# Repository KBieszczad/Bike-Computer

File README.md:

# Custom IoT Bike Computer

A low-power custom bicycle computer featuring speed measurement, GPS tracking, environmental sensing, and an OLED display. The hardware is designed from scratch with a custom PCB created in KiCad.

## Description

This project aims to build a standalone, power-efficient bike computer. At its core is the Seeed Studio **XIAO nRF52840**, a very energy efficient microcontroller with native Bluetooth Low Energy support.

The device combines data from a classic magnetic reed switch (for precise speed and distance tracking) with an external GPS module for recording traces. Additionally, it integrates a BME280 sensor to monitor environmental conditions (temperature, humidity, and barometric pressure).

### Technical Features
* **Super-Loop Architecture:** Runs on a non-blocking state machine utilizing hardware interrupts (ISR) and atomics for exact speed calculation and UI rendering, completely avoiding `delay()` functions.
* **Persistent Storage (LittleFS):** Automatically saves user settings, wheel circumference, and route history to the internal non-volatile flash memory.
* **GPS Trace Recording:** Caches GPS coordinates in the background while moving and writes directly to flash. Traces can be directly exported over USB Serial to a raw `.gpx` file compatible with for example Strava.
* **Dynamic Power Management:** Implements multiple power modes (Normal, Eco, Ultra Eco). The device sends standard CASIC protocol sleep commands to the GPS module and hardware sleep flags to the BME280 sensor to drastically cut power consumption when full tracking is not needed.

## Hardware Components

* **MCU:** Seeed Studio XIAO nRF52840
* **GPS Module:** ATGM336H
* **Environment Sensor:** BME280
* **Display:** 1.54" I2C OLED (SSD1309)
* **Sensors:** Magnetic Reed Switch (Normally Open)
* **Power:** 470mAh Li-Pol Battery with hardware switch

## Project Structure

```text
.
├── hardware/
│   ├── project.kicad_sch        # KiCad Schematic file
│   ├── project.kicad_pcb        # KiCad PCB layout file
│   └── img/                     # Schematic and PCB layout images
├── software/                    # PlatformIO Firmware files
└── README.md
```

## Visuals

### Schematic

### PCB

## Installation & Build

### Prerequisites
* **Visual Studio Code** with the **PlatformIO** extension installed.
* Required libraries are automatically managed by `platformio.ini`

### Installing & Flashing
1. **Clone the repository:**
```bash
git clone https://github.com/KBieszczad/Bike-Computer.git
```
2. **Open the `software` folder** in VS Code (PlatformIO).
3. **Connect your XIAO nRF52840** via USB-C.
4. **Build and Upload** the firmware using the PlatformIO build tools.

## Usage & Configuration

1. **Navigation:**
   * **Button 1 (Left):** Short press to cycle through the available screens (Main, Environment, History, GPS, Wheel Setup, Power Mode).
   * **Button 2 (Right):** Used to interact with the current screen (e.g., scroll menus, change settings).
2. **Recording a Trip:**
   * Ensure GPS is toggled `ON` in the GPS Settings screen. The device will automatically start tracking your route once satellites are locked and movement is detected.
   * To finish and save the trip into the device's history, navigate to the **Main Screen**, press and hold **Button 2** for 2 seconds. The trip history will update and distance will reset.
3. **Exporting GPX Track:**
   * Connect the bike computer to a PC via USB.
   * Open a Serial Monitor tool (e.g., in PlatformIO) set to `115200` baud.
   * Navigate to the **GPS SETTINGS** screen on the device, select **EXPORT ROUTE**, and hold Button 2.
   * The device will output raw XML data. Copy this text, save it as a `.gpx` file, and upload it directly to Strava or GPX Studio.

## Authors
Krzysztof Bieszczad
[@KBieszczad](https://github.com/KBieszczad)

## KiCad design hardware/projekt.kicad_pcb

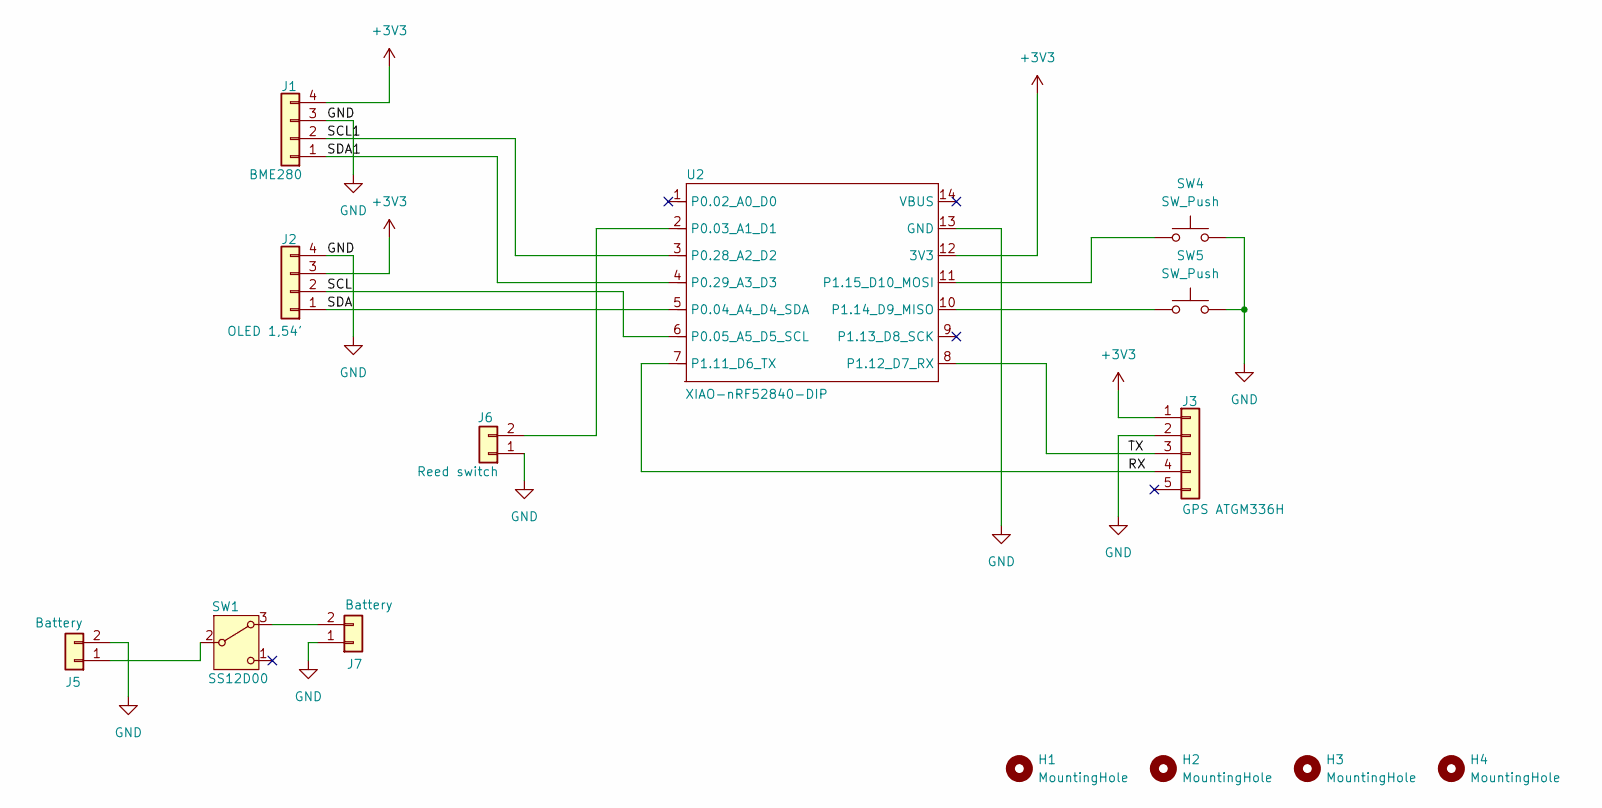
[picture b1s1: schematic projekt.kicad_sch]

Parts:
H1, H2, H3, H4: MountingHole; MountingHole_2.2mm_M2_Pad
J1: BME280; PinHeader_1x04_P2.54mm_Vertical
J2: OLED 1,54'; PinHeader_1x04_P2.54mm_Vertical
J3: GPS ATGM336H; PinHeader_1x05_P2.54mm_Vertical
J5: Battery; jst_2mm
J6: Reed switch; reed_switch
J7: Battery; PinHeader_1x02_P2.00mm_Vertical
SW1: SS12D00
SW4, SW5: SW_Push; tact_switch
U2: XIAO-nRF52840-DIP

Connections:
+3V3: J1.4, J2.3, J3.1, U2.12 (3V3)
/RX: J3.4, U2.7 (P1.11_D6_TX)
/SCL: J2.2, U2.6 (P0.05_A5_D5_SCL)
/SCL1: J1.2, U2.3 (P0.28_A2_D2)
/SDA: J2.1, U2.5 (P0.04_A4_D4_SDA)
/SDA1: J1.1, U2.4 (P0.29_A3_D3)
/TX: J3.3, U2.8 (P1.12_D7_RX)
GND: J1.3, J2.4, J3.2, J5.2, J6.1, J7.1, SW4.2, SW5.2, U2.13 (GND)
unnamed: J5.1, SW1.2 (B)
unnamed: J6.2, U2.2 (P0.03_A1_D1)
unnamed: J7.2, SW1.3 (A)
unnamed: SW5.1, U2.10 (P1.14_D9_MISO)
unnamed: SW4.1, U2.11 (P1.15_D10_MOSI)

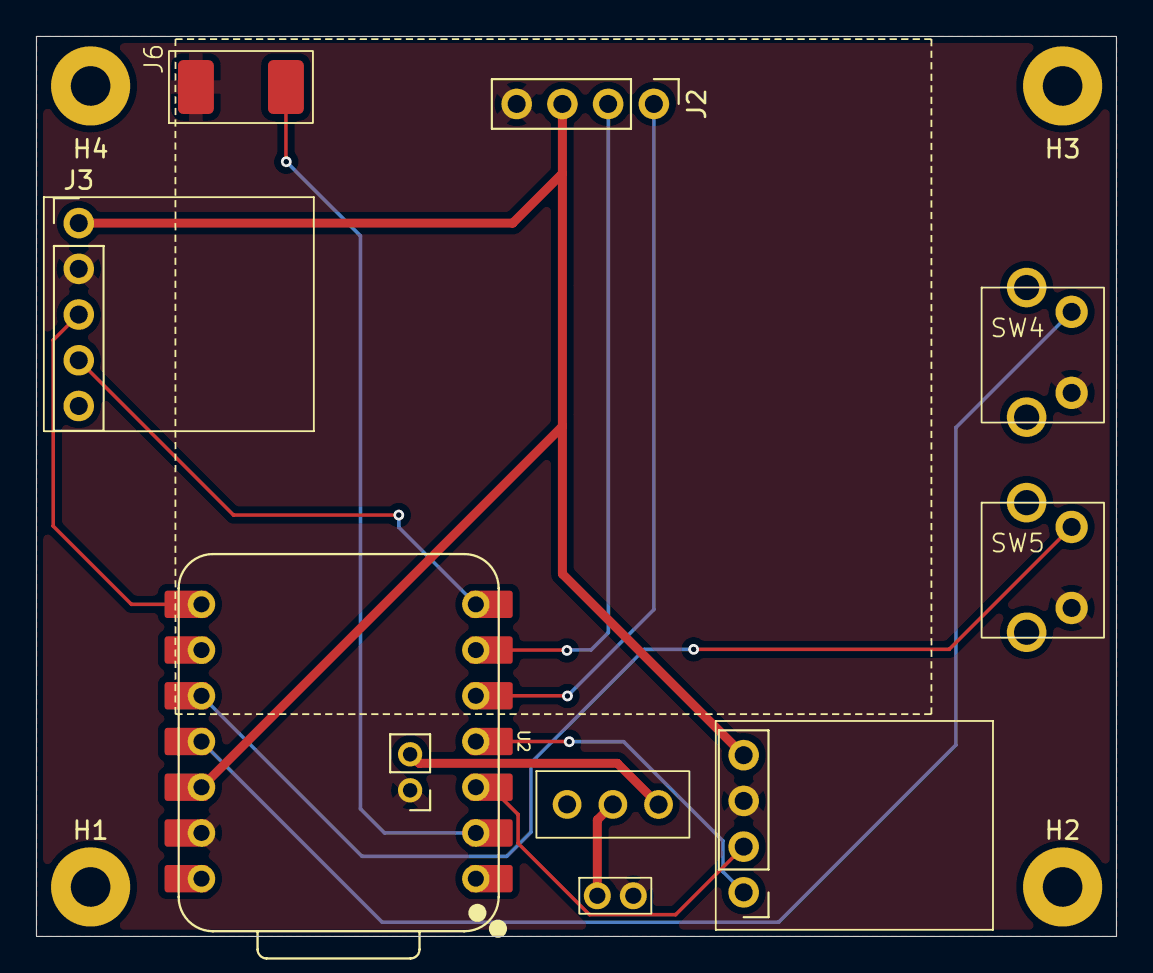
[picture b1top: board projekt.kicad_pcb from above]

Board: 2 copper layers, 60.0 x 50.0 mm, 14 parts (0 on the bottom side), 13 nets.

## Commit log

2026-05-16 add gerber files
2026-05-21 breadboard testing/prototype code
2026-05-21 add pcb layout images
2026-06-05 feat: lopaka design, machine state refactor
2026-06-06 feat: power modes, save gps to file
2026-06-13 perf: optimize ISR
2026-06-13 update files
2026-06-14 style: font, wheel sizes
2026-06-14 fix: gpx export
